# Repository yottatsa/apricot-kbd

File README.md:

# apricot-kbd
PS/2 to Apricot Xi keyboard translator

## For Arduino Uno

Simple to assemble version that could fit on a prototype board and could be hand-wired.

Firmware: [`apricot-kbd-uno.ino`](https://github.com/yottatsa/apricot-kbd/blob/main/apricot-kbd-uno.ino)

Schematics and PCB: [`schematics-assembly.pdf`](https://github.com/yottatsa/apricot-kbd/blob/main/schematics-assembly.pdf)

BOM:

* 18x24 2.54mm prototype board
* two 1x8 2.54mm pin headers
* [TSR_1-2450](http://www.tracopower.com/products/tsr1.pdf)
* [MC1488](https://www.ti.com/lit/ds/symlink/mc1488.pdf)
* [MC1489](https://www.ti.com/lit/ds/symlink/mc1489.pdf)
* PS/2 Y pigtail or any other way to connect a PS/2 keyboard
* DB9 serial cable pigtail or any other way to connect to Apricot keyboard port
* optional: two DIP-14 sockets

## Standalone ATmega328P

tbd

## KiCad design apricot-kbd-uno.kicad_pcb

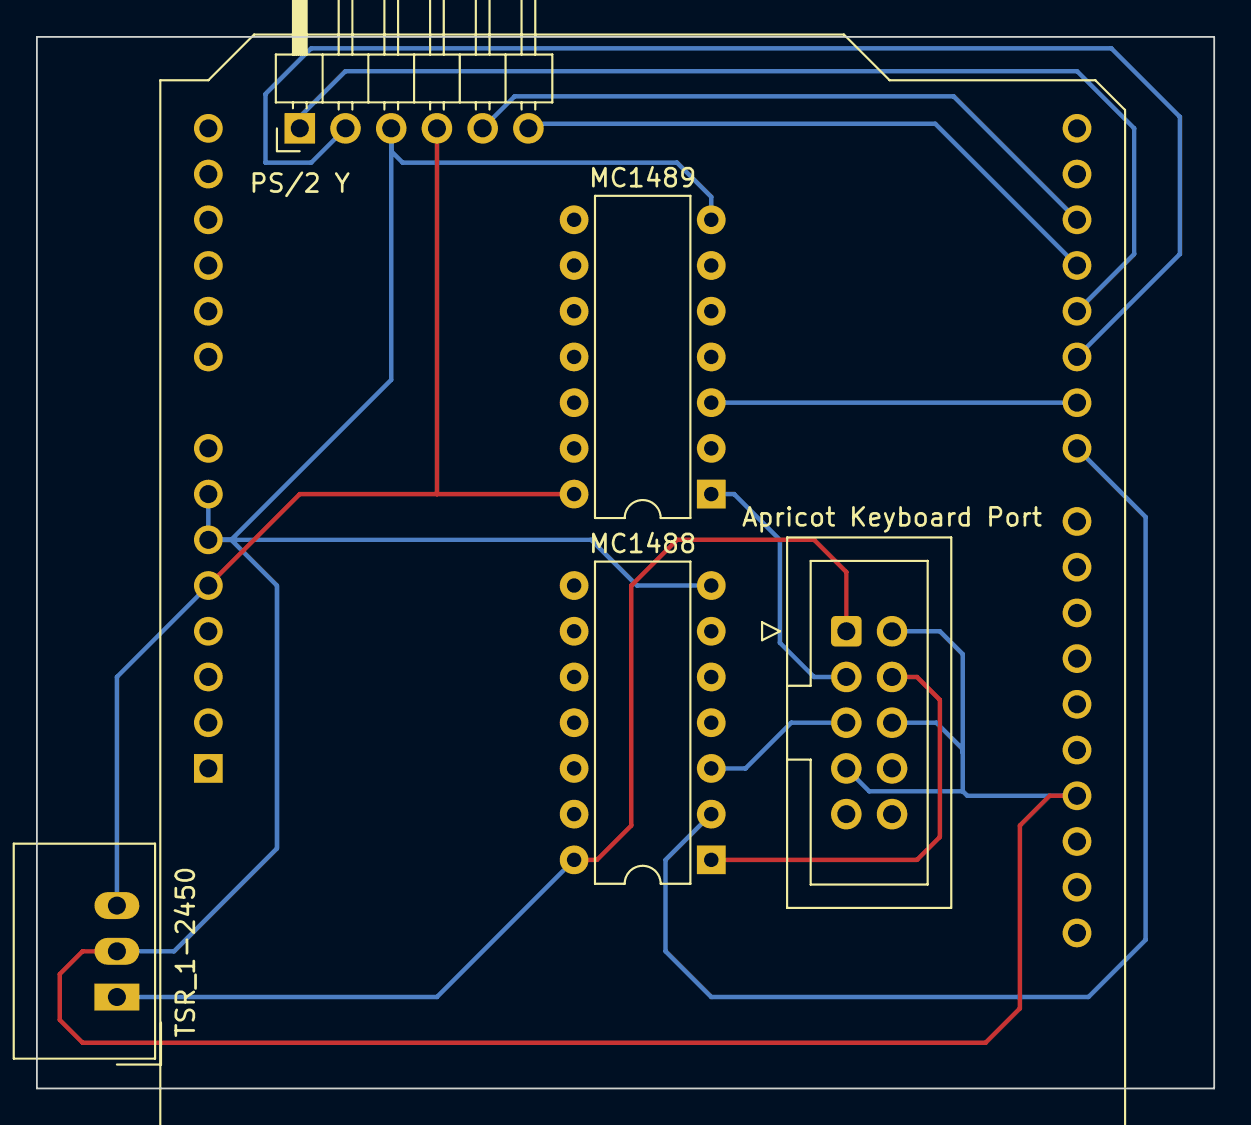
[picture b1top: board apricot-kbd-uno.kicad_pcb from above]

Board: 2 copper layers, 65.4 x 58.4 mm, 6 parts (0 on the bottom side), 12 nets.

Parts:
A101: Arduino_UNO_R3
J101: Apricot Keyboard Port; IDC-Header_2x05_P2.54mm_Vertical
J102: PS/2 Y; PinHeader_1x06_P2.54mm_Horizontal
U101: TSR_1-2450; Converter_DCDC_TRACO_TSR-1_THT
U102: MC1488; DIP-14_W7.62mm
U103: MC1489; DIP-14_W7.62mm

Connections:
5VDC: A101.5 (+5V), J102.4, U101.3 (Vout), U103.14 (VCC)
12VDC: J101.1, U101.1 (Vin), U102.14 (VCC+)
-12VDC: J101.4, U102.1 (VCC-)
EARTH: A101.6 (GND), A101.7 (GND), A101.29 (GND), J101.2, J101.6, J101.7, J102.3, U101.2 (GND), U102.7 (GND), U103.7 (GND)
KEYB.CLOCK: A101.17 (D2), J102.5
KEYB.DATA: A101.19 (D4), J102.1
MOUSE.CLOCK: A101.18 (D3), J102.6
MOUSE.DATA: A101.20 (D5), J102.2
RS232.IN: J101.3, U103.1 (1A)
RS232.OUT: J101.5, U102.3 (1Y)
UART.IN: A101.21 (D6), U103.3 (1Y)
UART.OUT: A101.22 (D7), U102.2 (1A)

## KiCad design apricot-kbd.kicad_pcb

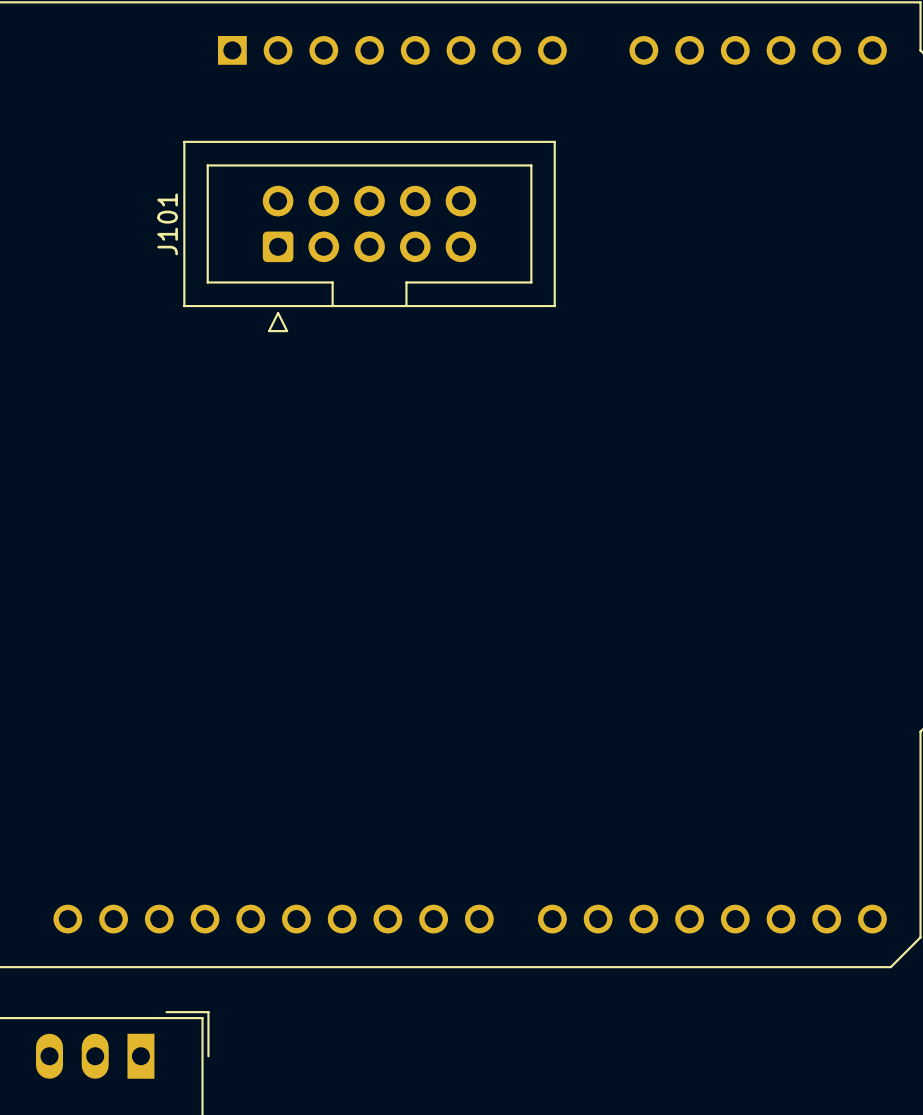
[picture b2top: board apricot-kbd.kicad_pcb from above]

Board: 2 copper layers, 3 parts (0 on the bottom side), 2 nets, no tracks yet.

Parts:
A101: Arduino_UNO_R3
J101: Apricot Keyboard Port; IDC-Header_2x05_P2.54mm_Vertical
U101: TSR_1-2450; Converter_DCDC_TRACO_TSR-1_THT

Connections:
12VDC: J101.1, U101.1 (Vin)
GND: J101.8, U101.2 (GND)

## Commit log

2023-04-11 initial
2023-04-11 docs
2023-04-11 assembly documentation. rev. uno-1.0
2023-04-11 reference implementation
